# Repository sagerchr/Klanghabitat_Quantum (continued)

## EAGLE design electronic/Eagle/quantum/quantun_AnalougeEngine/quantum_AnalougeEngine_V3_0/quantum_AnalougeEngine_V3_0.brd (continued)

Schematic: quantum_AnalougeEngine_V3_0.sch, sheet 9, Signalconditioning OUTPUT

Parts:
C17, C18, C19, C20, C23, C24: 100nF; C0603
D1, D2, D6, D7: 4148; SOD323-R
IC5, IC6, IC7: NE5532D; SO08
R1, R2, R4, R6, R13, R16, R31, R32: 100k; R0805
R3, R15: 0R; R0805
R5, R30: 180k; R0805
TP03, TP04: TPTHT; THT_PIN

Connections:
ADC1-IN3: R3.2, TP03.P$1; also elsewhere on the board
ADC2-IN10: R15.2, TP04.P$1; also elsewhere on the board
AGND: C17.2, C18.2, C19.2, C20.2, C23.2, C24.2, IC5.3 (+IN), IC5.5 (+IN), IC6.3 (+IN), IC6.5 (+IN); also elsewhere on the board
L/M_OUT(VCA1_OUT): IC7.3 (+IN); also elsewhere on the board
unnamed: D2.C, IC5.2 (-IN), R1.2, R6.1
unnamed: D1.C, D2.A, IC5.1 (OUT)
unnamed: D1.A, R4.1, R6.2
unnamed: IC5.6 (-IN), R4.2, R5.2, R13.1
unnamed: IC5.7 (OUT), R3.1, R13.2
unnamed: D7.C, IC6.2 (-IN), R2.2, R31.1
unnamed: D6.C, D7.A, IC6.1 (OUT)
unnamed: D6.A, R16.1, R31.2
unnamed: IC6.6 (-IN), R16.2, R30.2, R32.1
unnamed: IC6.7 (OUT), R15.1, R32.2
NET11: IC7.1 (OUT), IC7.2 (-IN), R1.1, R5.1
NET22: IC7.6 (-IN), IC7.7 (OUT), R2.1, R30.1
R/S_OUT(VCA2_OUT): IC7.5 (+IN); also elsewhere on the board
V+: C18.1, C20.1, C23.1, IC5.8 (V+), IC6.8 (V+), IC7.8 (V+); also elsewhere on the board
V-: C17.1, C19.1, C24.1, IC5.4 (V-), IC6.4 (V-), IC7.4 (V-); also elsewhere on the board

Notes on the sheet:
Präzisionsgleichrichter

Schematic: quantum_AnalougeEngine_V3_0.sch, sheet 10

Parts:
U1: NUCLEO-F429ZI; MODULE_NUCLEO-F429ZI

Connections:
+9V: U1.CN8_15 (VIN); also elsewhere on the board
ADC1-IN0: U1.CN11_28 (PA0); also elsewhere on the board
ADC1-IN3: U1.CN12_37 (PA3); also elsewhere on the board
ADC1-IN6: U1.CN12_13 (PA6)
ADC2-IN9: U1.CN12_24 (PB1); also elsewhere on the board
ADC2-IN10: U1.CN11_38 (PC0); also elsewhere on the board
ADC2-IN12: U1.CN11_35 (PC2)
ADC3-IN13: U1.CN11_37 (PC3)
ADC3-IN14: U1.CN12_38 (PF4)
ADC3-IN15: U1.CN12_36 (PF5)
DAC_OUT1: U1.CN11_32 (PA4); also elsewhere on the board
DAC_OUT2: U1.CN12_11 (PA5); also elsewhere on the board
DGND: U1.CN8_11 (GND_CN8), U1.CN8_13 (GND_CN8); also elsewhere on the board
RELAIS1: U1.CN11_58 (PG1); also elsewhere on the board
RELAIS2: U1.CN11_62 (PE6); also elsewhere on the board
RELAIS3: U1.CN11_64 (PG15); also elsewhere on the board
RELAIS4: U1.CN11_66 (PG10); also elsewhere on the board
RELAIS5: U1.CN11_65 (PG12); also elsewhere on the board
RELAIS6: U1.CN11_63 (PG9); also elsewhere on the board
USART6_TX: U1.CN12_4 (PC6)
USRAT6_RX: U1.CN12_19 (PC7)

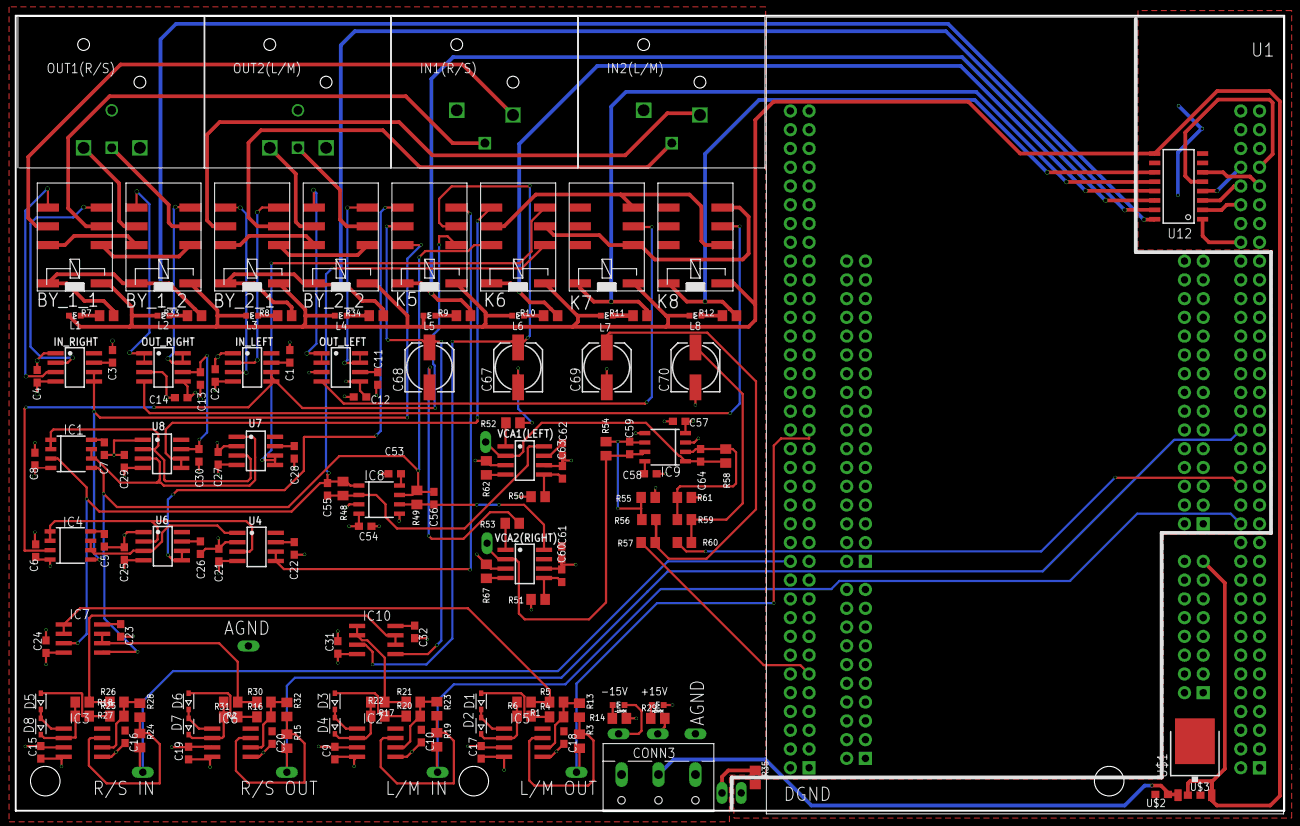
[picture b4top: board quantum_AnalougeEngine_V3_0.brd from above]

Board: 4 copper layers, 171.7 x 107.6 mm, 167 parts (0 on the bottom side), 111 nets.

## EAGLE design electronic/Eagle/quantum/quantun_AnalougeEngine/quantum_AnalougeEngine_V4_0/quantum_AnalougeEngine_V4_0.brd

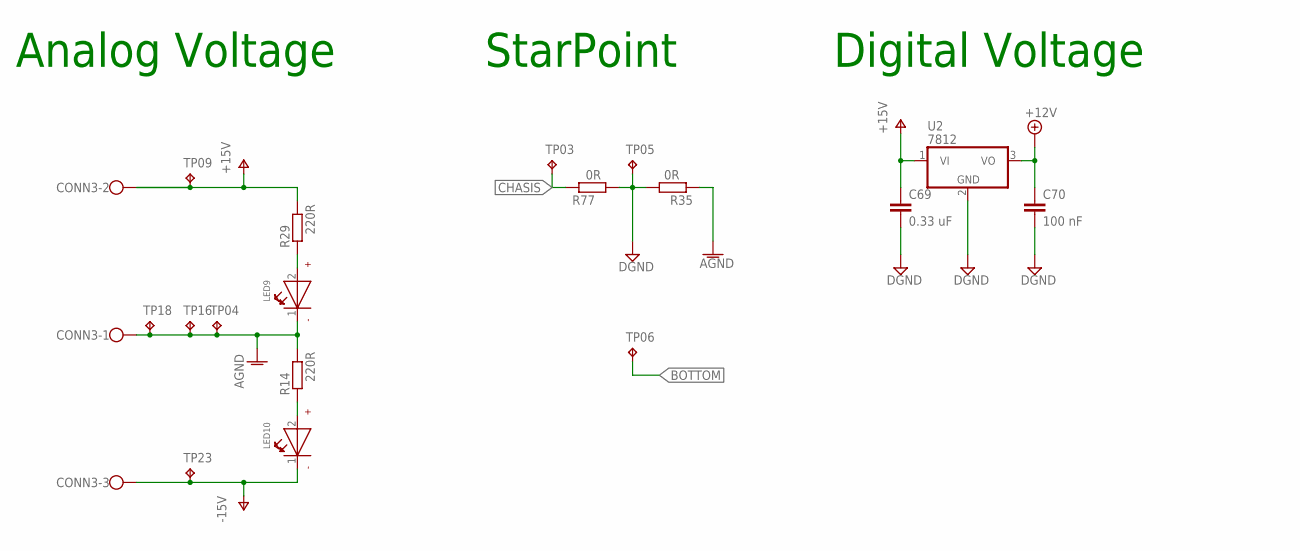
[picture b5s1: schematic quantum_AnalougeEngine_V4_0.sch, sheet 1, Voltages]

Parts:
C69: 0.33 uF; C0603
C70: 100 nF; C0603
CONN3: SCHRAUBKLEMME_3POL; W237-103
LED9, LED10: LED_GREEN_SMD; WL-SMCW_0603
R14, R29: 220R; R0603
R35, R77: 0R; R0603
TP03, TP04, TP05, TP06, TP09, TP16, TP18, TP23: TPTHT; THT_PIN
U2: 7812; TO252

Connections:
+12V: C70.1, U2.3 (VO); also elsewhere on the board
AGND: CONN3.1, LED9.1 (-), R14.2, R35.1, TP04.P$1, TP16.P$1, TP18.P$1; also elsewhere on the board
BOTTOM: TP06.P$1
CHASIS: R77.1, TP03.P$1; also elsewhere on the board
DGND: C69.2, C70.2, R35.2, R77.2, TP05.P$1, U2.2 (GND); also elsewhere on the board
unnamed: LED10.2 (+), R14.1
unnamed: LED9.2 (+), R29.1
V+: C69.1, CONN3.2, R29.2, TP09.P$1, U2.1 (VI); also elsewhere on the board
V-: CONN3.3, LED10.1 (-), TP23.P$1; also elsewhere on the board

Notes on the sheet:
StarPoint
Analog Voltage
Digital Voltage

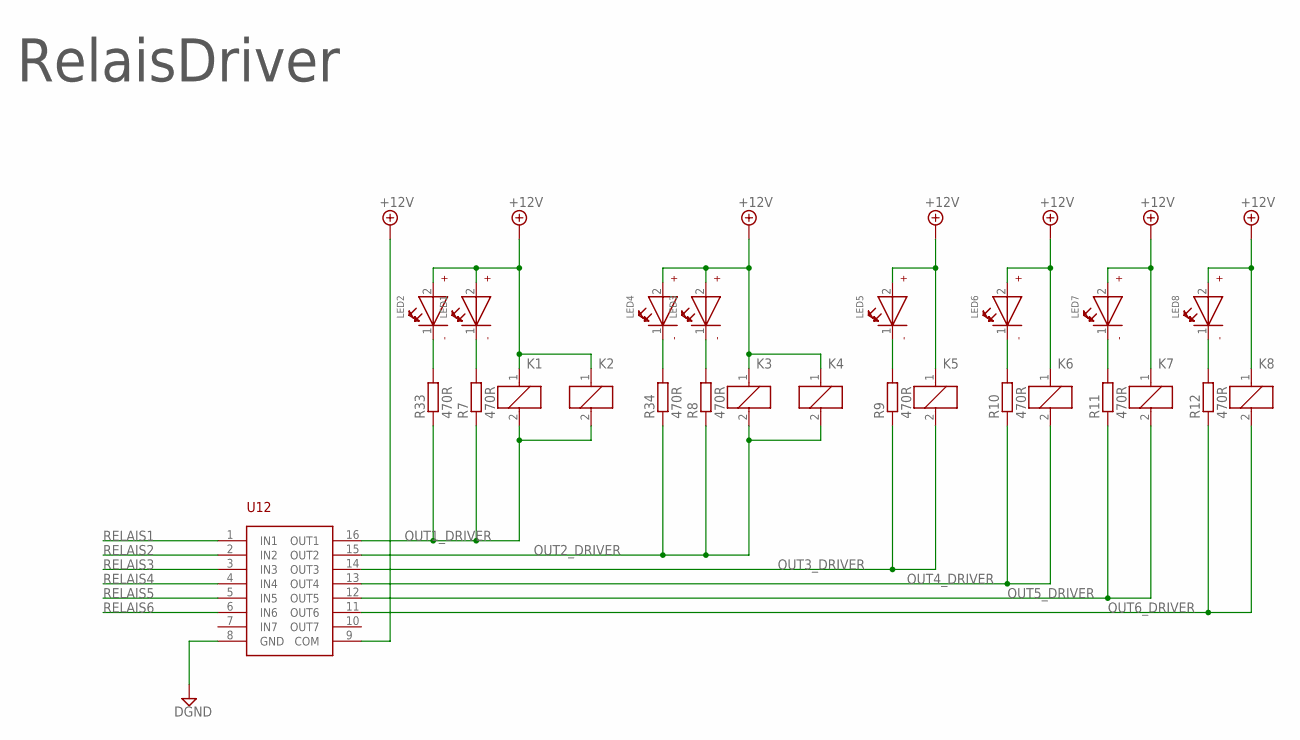
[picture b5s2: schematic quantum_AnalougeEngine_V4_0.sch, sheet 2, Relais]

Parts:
K1: K1; 351
K2: K2; 351
K3: K3; 351
K4: K4; 351
K5: K5; 351
K6: K6; 351
K7: K7; 351
K8: K8; 351
LED1, LED2, LED3, LED4, LED5, LED6, LED7, LED8: LED_BLUE_SMD; WL-SMCW_0603
R7, R8, R9, R10, R11, R12, R33, R34: 470R; R0603
U12: ULN2003; SOIC16

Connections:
+12V: K1.1, K2.1, K3.1, K4.1, K5.1, K6.1, K7.1, K8.1, LED1.2 (+), LED2.2 (+), LED3.2 (+), LED4.2 (+), LED5.2 (+), LED6.2 (+), LED7.2 (+), LED8.2 (+), U12.9 (COM); also elsewhere on the board
DGND: U12.8 (GND); also elsewhere on the board
unnamed: LED1.1 (-), R7.2
unnamed: LED3.1 (-), R8.2
unnamed: LED8.1 (-), R12.2
unnamed: LED7.1 (-), R11.2
unnamed: LED6.1 (-), R10.2
unnamed: LED5.1 (-), R9.2
unnamed: LED2.1 (-), R33.2
unnamed: LED4.1 (-), R34.2
OUT1_DRIVER: K1.2, K2.2, R7.1, R33.1, U12.16 (OUT1)
OUT2_DRIVER: K3.2, K4.2, R8.1, R34.1, U12.15 (OUT2)
OUT3_DRIVER: K5.2, R9.1, U12.14 (OUT3)
OUT4_DRIVER: K6.2, R10.1, U12.13 (OUT4)
OUT5_DRIVER: K7.2, R11.1, U12.12 (OUT5)
OUT6_DRIVER: K8.2, R12.1, U12.11 (OUT6)
RELAIS1: U12.1 (IN1); also elsewhere on the board
RELAIS2: U12.2 (IN2); also elsewhere on the board
RELAIS3: U12.3 (IN3); also elsewhere on the board
RELAIS4: U12.4 (IN4); also elsewhere on the board
RELAIS5: U12.5 (IN5); also elsewhere on the board
RELAIS6: U12.6 (IN6); also elsewhere on the board

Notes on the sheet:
RelaisDriver

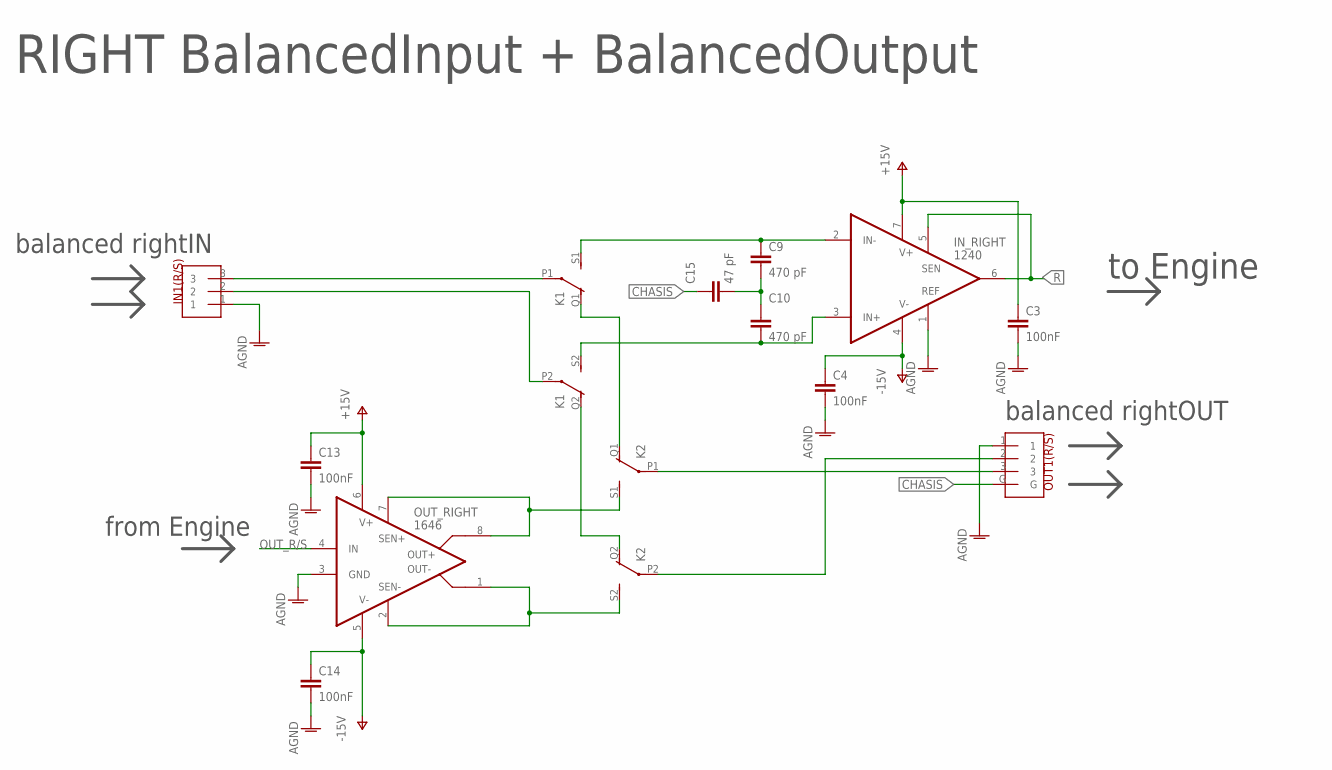
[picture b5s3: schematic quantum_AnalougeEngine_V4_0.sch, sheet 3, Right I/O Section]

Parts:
C3, C4, C13, C14: 100nF; C0603
C9, C10: 470 pF; C0603
C15: 47 pF; C0603
IN1(R/S): NEUTRIK_NC3FAH
IN_RIGHT: 1240; SO08
K1: K1; 351
K2: K2; 351
OUT1(R/S): NEUTRIK_NC3MAH
OUT_RIGHT: 1646; SO08

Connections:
AGND: C3.2, C4.2, C13.2, C14.2, IN1(R/S).1, IN_RIGHT.1 (REF), OUT1(R/S).1, OUT_RIGHT.3 (GND); also elsewhere on the board
CHASIS: C15.1, OUT1(R/S).G; also elsewhere on the board
unnamed: C9.1, IN_RIGHT.2 (IN-), K1.S1 (S)
unnamed: C10.2, IN_RIGHT.3 (IN+), K1.S2 (S)
unnamed: C9.2, C10.1, C15.2
unnamed: K1.Q1 (O), K2.Q1 (O)
unnamed: K1.Q2 (O), K2.Q2 (O)
unnamed: IN1(R/S).2, K1.P2
unnamed: IN1(R/S).3, K1.P1
unnamed: K2.P2, OUT1(R/S).2
unnamed: K2.P1, OUT1(R/S).3
OUT_R/S: OUT_RIGHT.4 (IN); also elsewhere on the board
R: IN_RIGHT.5 (SEN), IN_RIGHT.6 (OUT); also elsewhere on the board
R/S_OUT+: K2.S1 (S), OUT_RIGHT.7 (SEN+), OUT_RIGHT.8 (OUT+)
R/S_OUT-: K2.S2 (S), OUT_RIGHT.1 (OUT-), OUT_RIGHT.2 (SEN-)
V+: C3.1, C13.1, IN_RIGHT.7 (V+), OUT_RIGHT.6 (V+); also elsewhere on the board
V-: C4.1, C14.1, IN_RIGHT.4 (V-), OUT_RIGHT.5 (V-); also elsewhere on the board

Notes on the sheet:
RIGHT BalancedInput + BalancedOutput
balanced rightIN
balanced rightOUT
from Engine
to Engine

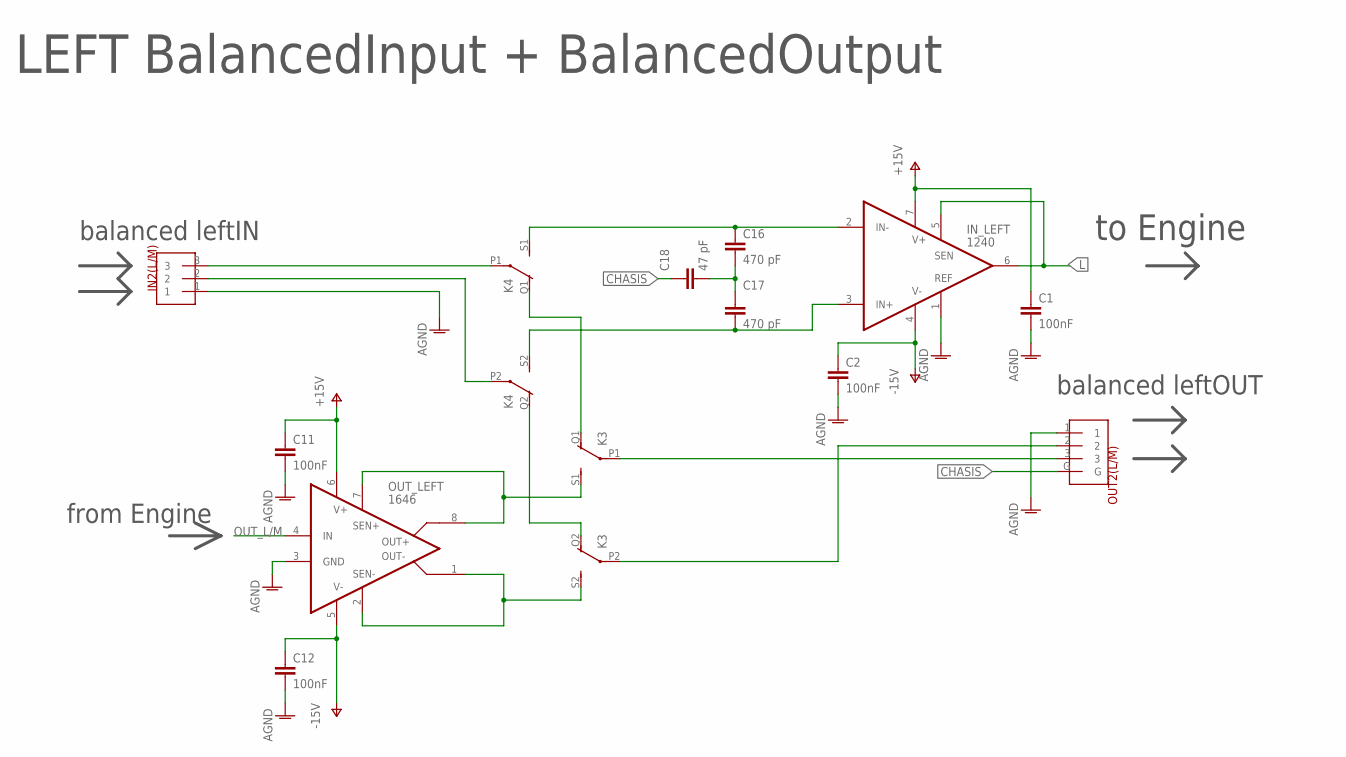
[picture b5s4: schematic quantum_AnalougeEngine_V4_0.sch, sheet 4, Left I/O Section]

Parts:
C1, C2, C11, C12: 100nF; C0603
C16, C17: 470 pF; C0603
C18: 47 pF; C0603
IN2(L/M): NEUTRIK_NC3FAH
IN_LEFT: 1240; SO08
K3: K3; 351
K4: K4; 351
OUT2(L/M): NEUTRIK_NC3MAH
OUT_LEFT: 1646; SO08

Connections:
AGND: C1.2, C2.2, C11.2, C12.2, IN2(L/M).1, IN_LEFT.1 (REF), OUT2(L/M).1, OUT_LEFT.3 (GND); also elsewhere on the board
CHASIS: C18.1, OUT2(L/M).G; also elsewhere on the board
L: IN_LEFT.5 (SEN), IN_LEFT.6 (OUT); also elsewhere on the board
L/M_OUT+: K3.S1 (S), OUT_LEFT.7 (SEN+), OUT_LEFT.8 (OUT+)
L/M_OUT-: K3.S2 (S), OUT_LEFT.1 (OUT-), OUT_LEFT.2 (SEN-)
unnamed: C17.2, IN_LEFT.3 (IN+), K4.S2 (S)
unnamed: C16.2, C17.1, C18.2
unnamed: C16.1, IN_LEFT.2 (IN-), K4.S1 (S)
unnamed: K3.P1, OUT2(L/M).3
unnamed: K3.P2, OUT2(L/M).2
unnamed: IN2(L/M).3, K4.P1
unnamed: IN2(L/M).2, K4.P2
unnamed: K3.Q1 (O), K4.Q1 (O)
unnamed: K3.Q2 (O), K4.Q2 (O)
OUT_L/M: OUT_LEFT.4 (IN); also elsewhere on the board
V+: C1.1, C11.1, IN_LEFT.7 (V+), OUT_LEFT.6 (V+); also elsewhere on the board
V-: C2.1, C12.1, IN_LEFT.4 (V-), OUT_LEFT.5 (V-); also elsewhere on the board

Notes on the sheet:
balanced leftIN
balanced leftOUT
from Engine
to Engine
LEFT BalancedInput + BalancedOutput

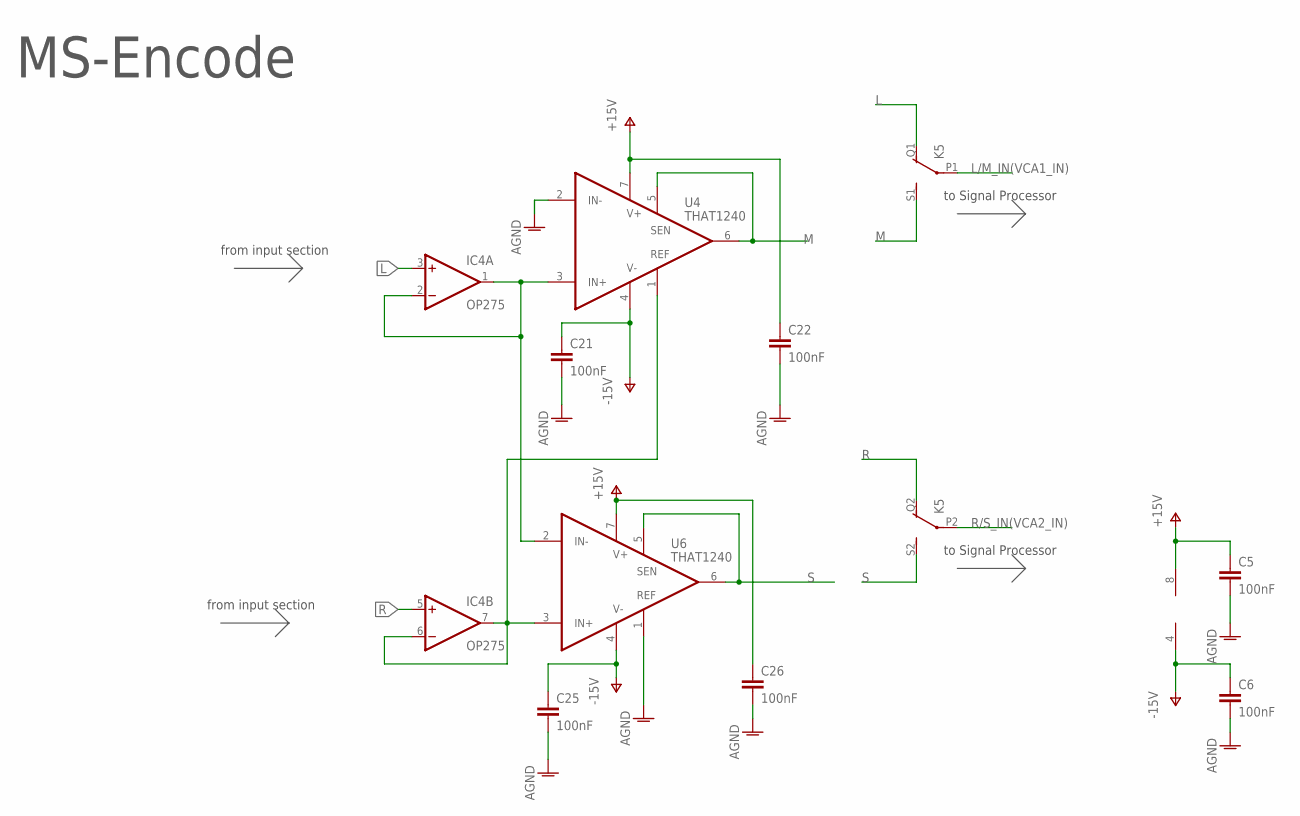
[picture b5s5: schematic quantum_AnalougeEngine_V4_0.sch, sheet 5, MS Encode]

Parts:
C5, C6, C21, C22, C25, C26: 100nF; C0603
IC4: OP275; SOIC8
K5: K5; 351
U4, U6: THAT1240; SO08

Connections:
AGND: C5.2, C6.2, C21.2, C22.2, C25.2, C26.2, U4.2 (IN-), U6.1 (REF); also elsewhere on the board
L: IC4.3 (+IN), K5.Q1 (O); also elsewhere on the board
L/M_IN(VCA1_IN): K5.P1; also elsewhere on the board
M: K5.S1 (S), U4.5 (SEN), U4.6 (OUT)
unnamed: IC4.1 (OUT), IC4.2 (-IN), U4.3 (IN+), U6.2 (IN-)
unnamed: IC4.6 (-IN), IC4.7 (OUT), U4.1 (REF), U6.3 (IN+)
R: IC4.5 (+IN), K5.Q2 (O); also elsewhere on the board
R/S_IN(VCA2_IN): K5.P2; also elsewhere on the board
S: K5.S2 (S), U6.5 (SEN), U6.6 (OUT)
V+: C5.1, C22.1, C26.1, IC4.8 (V+), U4.7 (V+), U6.7 (V+); also elsewhere on the board
V-: C6.1, C21.1, C25.1, IC4.4 (V-), U4.4 (V-), U6.4 (V-); also elsewhere on the board

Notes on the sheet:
to Signal Processor
MS-Encode
from input section

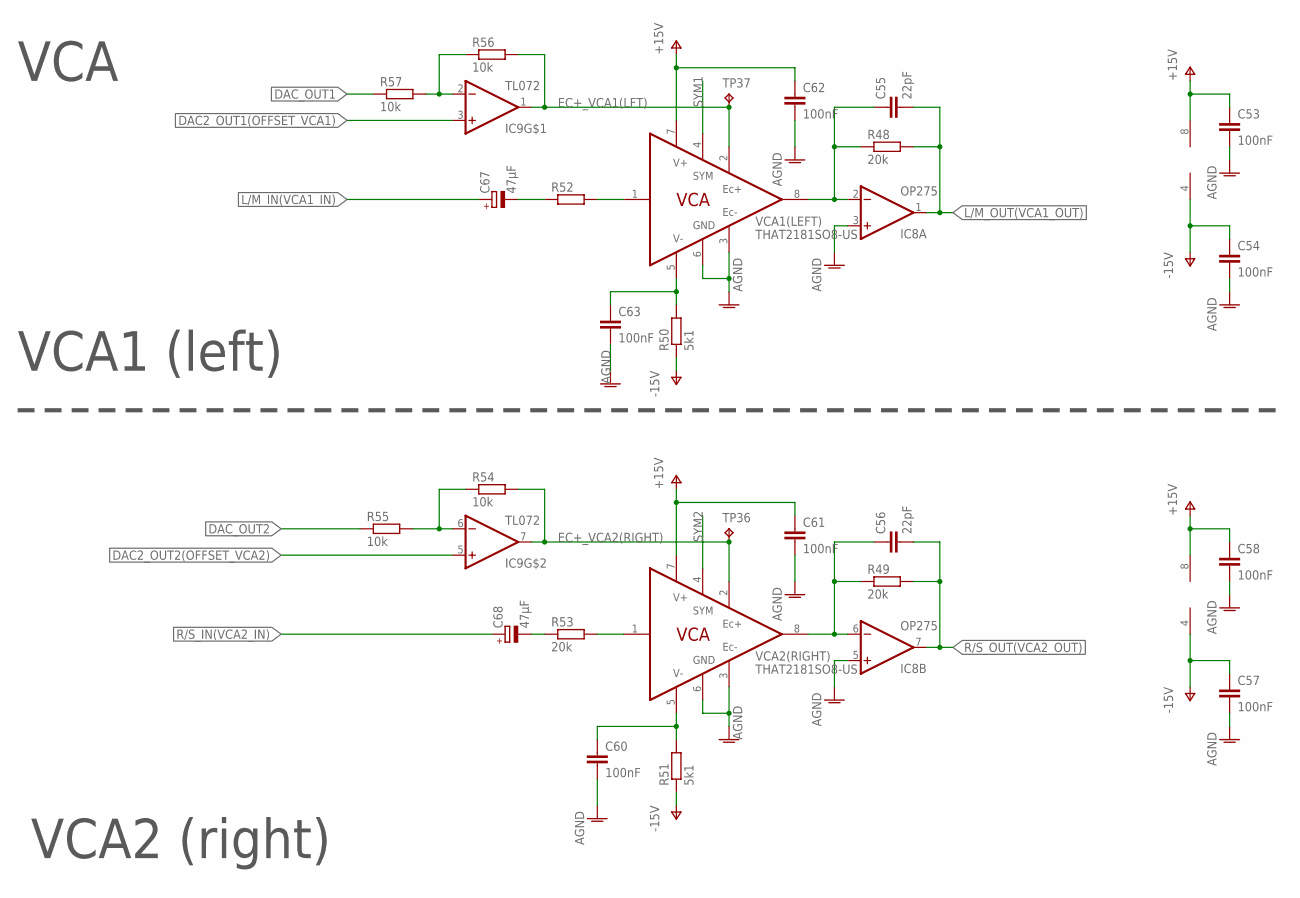
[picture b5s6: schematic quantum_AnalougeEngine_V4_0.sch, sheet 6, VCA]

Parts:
C53, C54, C57, C58, C60, C61, C62, C63: 100nF; C0603
C55, C56: 22pF; C0603
C67, C68: 47µF; CAPAE400X550N
IC8: OP275; SOIC8
IC9: TL072; SOIC8
R48, R49, R52, R53: 20k; R0603
R50, R51: 5k1; R0603
R54, R55, R56, R57: 10k; R0603
TP36, TP37: TPTHT; THT_PIN
VCA1(LEFT), VCA2(RIGHT): THAT2181SO8-US; SO08

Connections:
AGND: C53.2, C54.2, C57.2, C58.2, C60.2, C61.2, C62.2, C63.2, IC8.3 (+IN), IC8.5 (+IN), VCA1(LEFT).3 (EC-), VCA1(LEFT).6 (GND), VCA2(RIGHT).3 (EC-), VCA2(RIGHT).6 (GND); also elsewhere on the board
DAC2_OUT1(OFFSET_VCA1): IC9.3 (+IN); also elsewhere on the board
DAC2_OUT2(OFFSET_VCA2): IC9.5 (+IN); also elsewhere on the board
DAC_OUT1: R57.1; also elsewhere on the board
DAC_OUT2: R55.1; also elsewhere on the board
EC+_VCA1(LFT): IC9.1 (OUT), R56.2, TP37.P$1, VCA1(LEFT).2 (EC+)
EC+_VCA2(RIGHT): IC9.7 (OUT), R54.2, TP36.P$1, VCA2(RIGHT).2 (EC+)
L/M_IN(VCA1_IN): C67.1 (+); also elsewhere on the board
L/M_OUT(VCA1_OUT): C55.2, IC8.1 (OUT), R48.2; also elsewhere on the board
unnamed: IC9.2 (-IN), R56.1, R57.2
unnamed: C55.1, IC8.2 (-IN), R48.1, VCA1(LEFT).8 (OUT)
unnamed: R52.2, VCA1(LEFT).1 (IN)
unnamed: C67.2 (-), R52.1
unnamed: C56.1, IC8.6 (-IN), R49.1, VCA2(RIGHT).8 (OUT)
unnamed: C60.1, R51.2, VCA2(RIGHT).5 (V-)
unnamed: C68.2 (-), R53.1
unnamed: R53.2, VCA2(RIGHT).1 (IN)
unnamed: C63.1, R50.2, VCA1(LEFT).5 (V-)
unnamed: IC9.6 (-IN), R54.1, R55.2
R/S_IN(VCA2_IN): C68.1 (+); also elsewhere on the board
R/S_OUT(VCA2_OUT): C56.2, IC8.7 (OUT), R49.2; also elsewhere on the board
SYM1: VCA1(LEFT).4 (SYM); also elsewhere on the board
SYM2: VCA2(RIGHT).4 (SYM); also elsewhere on the board
V+: C53.1, C58.1, C61.1, C62.1, IC8.8 (V+), IC9.8 (V+), VCA1(LEFT).7 (V+), VCA2(RIGHT).7 (V+); also elsewhere on the board
V-: C54.1, C57.1, IC8.4 (V-), IC9.4 (V-), R50.1, R51.1; also elsewhere on the board

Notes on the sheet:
VCA
VCA1 (left)
VCA2 (right)

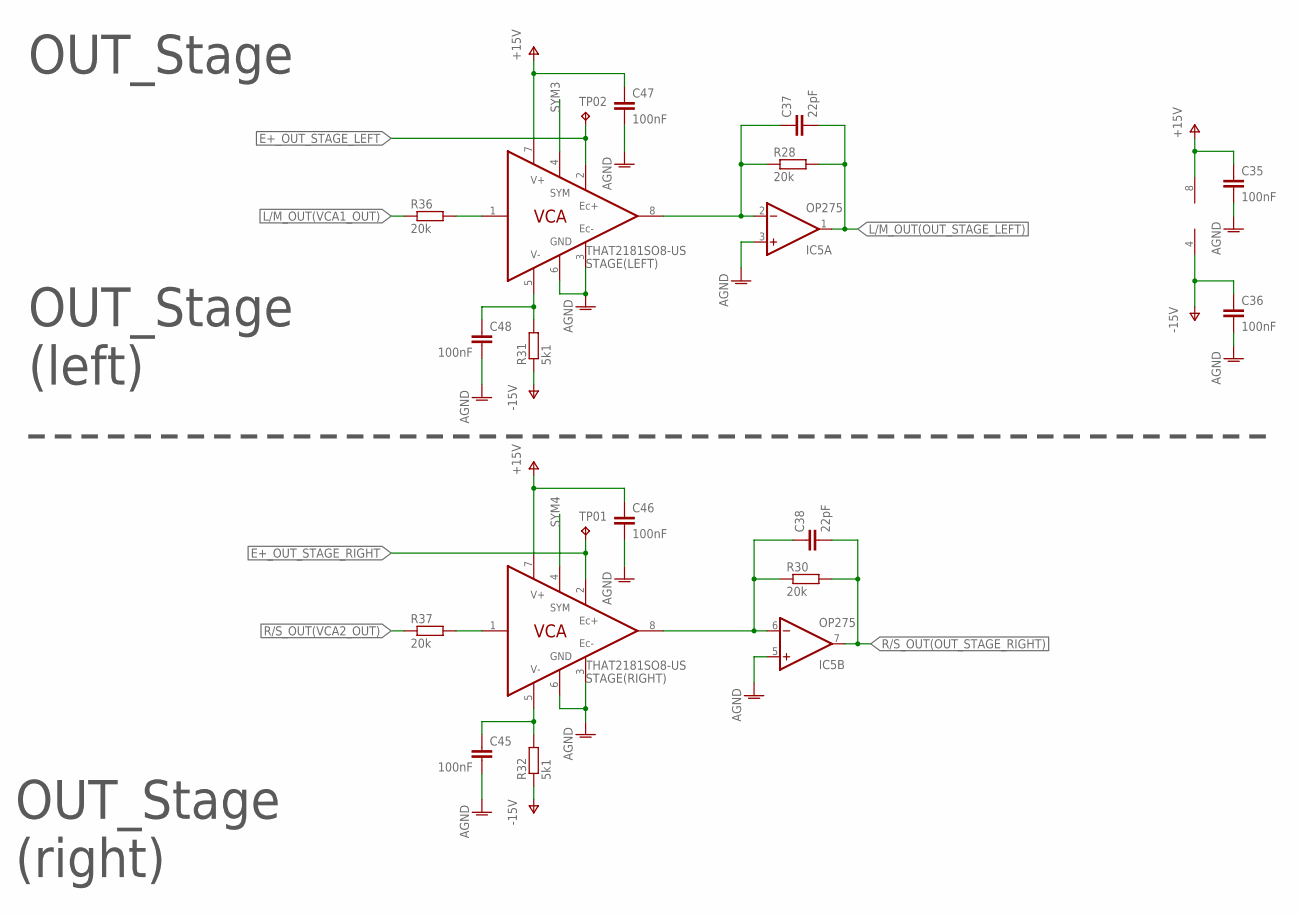
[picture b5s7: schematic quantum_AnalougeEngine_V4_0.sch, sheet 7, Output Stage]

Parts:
C35, C36, C45, C46, C47, C48: 100nF; C0603
C37, C38: 22pF; C0603
IC5: OP275; SOIC8
R28, R30, R36, R37: 20k; R0603
R31, R32: 5k1; R0603
STAGE(LEFT): THAT2181SO8-US; SO08
STAGE(RIGHT): THAT2181SO8-US; SO08
TP01, TP02: TPTHT; THT_PIN

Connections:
AGND: C35.2, C36.2, C45.2, C46.2, C47.2, C48.2, IC5.3 (+IN), IC5.5 (+IN), STAGE(LEFT).3 (EC-), STAGE(LEFT).6 (GND), STAGE(RIGHT).3 (EC-), STAGE(RIGHT).6 (GND); also elsewhere on the board
E+_OUT_STAGE_LEFT: STAGE(LEFT).2 (EC+), TP02.P$1; also elsewhere on the board
E+_OUT_STAGE_RIGHT: STAGE(RIGHT).2 (EC+), TP01.P$1; also elsewhere on the board
L/M_OUT(OUT_STAGE_LEFT): C37.2, IC5.1 (OUT), R28.2; also elsewhere on the board
L/M_OUT(VCA1_OUT): R36.1; also elsewhere on the board
unnamed: C37.1, IC5.2 (-IN), R28.1, STAGE(LEFT).8 (OUT)
unnamed: C38.1, IC5.6 (-IN), R30.1, STAGE(RIGHT).8 (OUT)
unnamed: C45.1, R32.2, STAGE(RIGHT).5 (V-)
unnamed: R36.2, STAGE(LEFT).1 (IN)
unnamed: R37.2, STAGE(RIGHT).1 (IN)
unnamed: C48.1, R31.2, STAGE(LEFT).5 (V-)
R/S_OUT(OUT_STAGE_RIGHT): C38.2, IC5.7 (OUT), R30.2; also elsewhere on the board
R/S_OUT(VCA2_OUT): R37.1; also elsewhere on the board
SYM3: STAGE(LEFT).4 (SYM); also elsewhere on the board
SYM4: STAGE(RIGHT).4 (SYM); also elsewhere on the board
V+: C35.1, C46.1, C47.1, IC5.8 (V+), STAGE(LEFT).7 (V+), STAGE(RIGHT).7 (V+); also elsewhere on the board
V-: C36.1, IC5.4 (V-), R31.1, R32.1; also elsewhere on the board

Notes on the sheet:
OUT_Stage
OUT_Stage (left)
OUT_Stage (right)

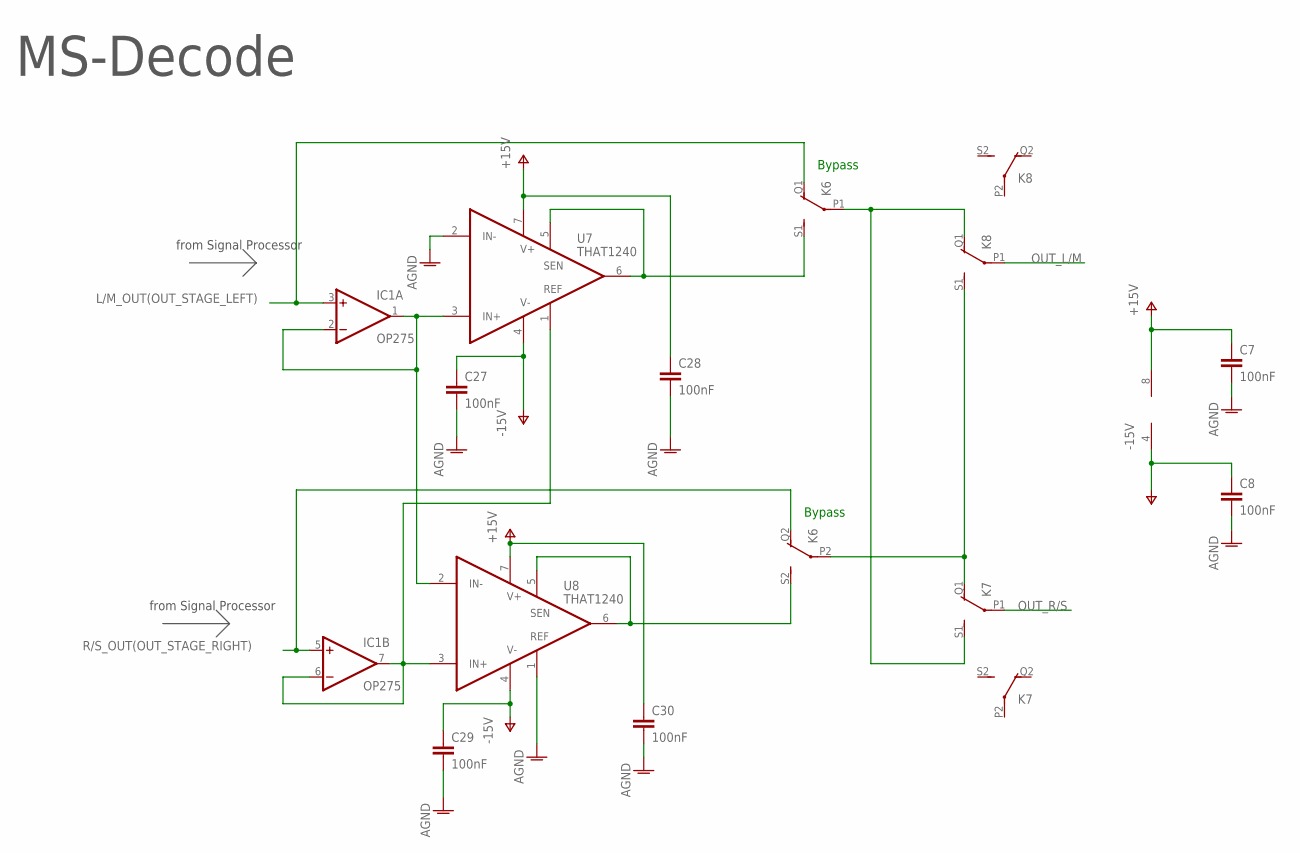
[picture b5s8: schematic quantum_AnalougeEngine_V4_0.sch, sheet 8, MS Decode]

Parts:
C7, C8, C27, C28, C29, C30: 100nF; C0603
IC1: OP275; SOIC8
K6: K6; 351
K7: K7; 351
K8: K8; 351
U7, U8: THAT1240; SO08

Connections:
AGND: C7.2, C8.2, C27.2, C28.2, C29.2, C30.2, U7.2 (IN-), U8.1 (REF); also elsewhere on the board
L/M_OUT(OUT_STAGE_LEFT): IC1.3 (+IN), K6.Q1 (O); also elsewhere on the board
M1: K6.S1 (S), U7.5 (SEN), U7.6 (OUT)
unnamed: K6.P1, K7.S1 (S), K8.Q1 (O)
unnamed: K6.P2, K7.Q1 (O), K8.S1 (S)
unnamed: IC1.6 (-IN), IC1.7 (OUT), U7.1 (REF), U8.3 (IN+)
unnamed: IC1.1 (OUT), IC1.2 (-IN), U7.3 (IN+), U8.2 (IN-)
OUT_L/M: K8.P1; also elsewhere on the board
OUT_R/S: K7.P1; also elsewhere on the board
R/S_OUT(OUT_STAGE_RIGHT): IC1.5 (+IN), K6.Q2 (O); also elsewhere on the board
S1: K6.S2 (S), U8.5 (SEN), U8.6 (OUT)
V+: C7.1, C28.1, C30.1, IC1.8 (V+), U7.7 (V+), U8.7 (V+); also elsewhere on the board
V-: C8.1, C27.1, C29.1, IC1.4 (V-), U7.4 (V-), U8.4 (V-); also elsewhere on the board

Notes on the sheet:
from Signal Processor
MS-Decode
Bypass

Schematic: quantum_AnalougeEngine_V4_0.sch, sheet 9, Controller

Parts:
U1: NUCLEO-F429ZI; MODULE_NUCLEO-F429ZI

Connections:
+3V3_STM32: U1.CN11_16 (+3.3V); also elsewhere on the board
+5V_STM32: U1.CN11_18 (+5V); also elsewhere on the board
+12V: U1.CN8_15 (VIN); also elsewhere on the board
ADC1-IN0: U1.CN11_28 (PA0); also elsewhere on the board
ADC1-IN3: U1.CN12_37 (PA3); also elsewhere on the board
ADC1-IN6: U1.CN12_13 (PA6)
ADC2-IN9: U1.CN12_24 (PB1)
ADC2-IN10: U1.CN11_38 (PC0)
ADC2-IN12: U1.CN11_35 (PC2)
ADC3-IN13: U1.CN11_37 (PC3)
ADC3-IN14: U1.CN12_38 (PF4)
ADC3-IN15: U1.CN12_36 (PF5)
BUSY: U1.CN11_44 (PG3); also elsewhere on the board
CS: U1.CN11_45 (PD7); also elsewhere on the board
CS_DAC1: U1.CN12_27 (PB4); also elsewhere on the board
CS_DAC2: U1.CN12_29 (PB5); also elsewhere on the board
CV_A_B: U1.CN11_3 (PC12); also elsewhere on the board
DAC_OUT1: U1.CN11_32 (PA4); also elsewhere on the board
DAC_OUT2: U1.CN12_11 (PA5); also elsewhere on the board
DB0: U1.CN10_33 (D34/PE0/TIMER_B_ETR), U1.CN12_64 (PE0); also elsewhere on the board
DB1: U1.CN11_61 (PE1); also elsewhere on the board
DB2: U1.CN9_14 (D56/PE2/SAI_A_MCLK), U1.CN10_25 (D31/PE2); also elsewhere on the board
DB3: U1.CN9_22 (D60/PE3/SAI_B_SD), U1.CN11_47 (PE3); also elsewhere on the board
DB4: U1.CN9_16 (D57/PE4/SAI_A_FS); also elsewhere on the board
DB5: U1.CN9_18 (D58/PE5/SAI_A_SCK); also elsewhere on the board
DB6: U1.CN9_20 (D59/PE6/SAI_A_SD), U1.CN11_62 (PE6); also elsewhere on the board
DB7: U1.CN10_20 (D41/PE7/TIMER_A_ETR), U1.CN12_44 (PE7); also elsewhere on the board
DB8: U1.CN10_18 (D42/PE8/TIMER_A_PWM1N); also elsewhere on the board
DB9: U1.CN10_4 (D6/PE9/TIMER_A_PWM1), U1.CN12_52 (PE9); also elsewhere on the board
DB10: U1.CN10_24 (D40/PE10/TIMER_A_PWM2N), U1.CN12_47 (PE10); also elsewhere on the board
DB11: U1.CN10_6 (D5/PE11/TIMER_A_PWM2); also elsewhere on the board
DB12: U1.CN10_26 (D39/PE12/TIMER_A_PWM3N), U1.CN12_49 (PE12); also elsewhere on the board
DB13: U1.CN10_10 (D3/PE13/TIMER_A_PWM3), U1.CN12_55 (PE13); also elsewhere on the board
DB14: U1.CN10_28 (D38/PE14), U1.CN12_51 (PE14); also elsewhere on the board
DB15: U1.CN12_53 (PE15); also elsewhere on the board
DGND: U1.CN8_11 (GND_CN8), U1.CN8_13 (GND_CN8); also elsewhere on the board
DIN_DAC: U1.CN9_5 (A2/PC3); also elsewhere on the board
FRST: U1.CN11_43 (PD6); also elsewhere on the board
OS0: U1.CN12_2 (PC8); also elsewhere on the board
OS1: U1.CN12_1 (PC9); also elsewhere on the board
OS2: U1.CN11_1 (PC10); also elsewhere on the board
RANGE: U1.CN11_2 (PC11); also elsewhere on the board
RD: U1.CN11_4 (PD2); also elsewhere on the board
RELAIS1: U1.CN11_58 (PG1); also elsewhere on the board
RELAIS2: U1.CN11_59 (PG0); also elsewhere on the board
RELAIS3: U1.CN11_64 (PG15); also elsewhere on the board
RELAIS4: U1.CN11_66 (PG10); also elsewhere on the board
RELAIS5: U1.CN11_65 (PG12); also elsewhere on the board
RELAIS6: U1.CN11_63 (PG9); also elsewhere on the board
RESET: U1.CN11_42 (PG2); also elsewhere on the board
SCLK_DAC: U1.CN12_25 (PB10); also elsewhere on the board
SWCLK: U1.CN11_15 (PA14)
SWDIO: U1.CN11_13 (PA13)
USART6_TX: U1.CN12_4 (PC6)
USRAT6_RX: U1.CN12_19 (PC7)

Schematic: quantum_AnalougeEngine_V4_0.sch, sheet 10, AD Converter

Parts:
R1, R4, R5, R6, R13, R15, R16, R17, R18, R19, R20, R21, R22, R23, R24, R25, R26, R27: 10k; R0603
R2, R3: 100k; R0603
U3: AD7606_EVALBOARD

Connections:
+3V3_STM32: R1.2; also elsewhere on the board
+5V_STM32: U3.+5V; also elsewhere on the board
ADC1-IN0: R3.1, R4.2; also elsewhere on the board
ADC1-IN3: R1.1, R2.2; also elsewhere on the board
AGND: R4.1, R6.1, R15.1, R16.1, R23.1, R24.1, R25.1, R26.1, R27.1, U3.G1, U3.G2, U3.G3, U3.G4, U3.G5, U3.G6, U3.G7, U3.G8; also elsewhere on the board
BUSY: U3.BUSY; also elsewhere on the board
CS: U3.CS; also elsewhere on the board
CV_A_B: U3.CVA, U3.CVB; also elsewhere on the board
DB0: U3.DB0; also elsewhere on the board
DB1: U3.DB1; also elsewhere on the board
DB2: U3.DB2; also elsewhere on the board
DB3: U3.DB3; also elsewhere on the board
DB4: U3.DB4; also elsewhere on the board
DB5: U3.DB5; also elsewhere on the board
DB6: U3.DB6; also elsewhere on the board
DB7: U3.DB7; also elsewhere on the board
DB8: U3.DB8; also elsewhere on the board
DB9: U3.DB9; also elsewhere on the board
DB10: U3.DB10; also elsewhere on the board
DB11: U3.DB11; also elsewhere on the board
DB12: U3.DB12; also elsewhere on the board
DB13: U3.DB13; also elsewhere on the board
DB14: U3.DB14; also elsewhere on the board
DB15: U3.DB15; also elsewhere on the board
DGND: U3.GND; also elsewhere on the board
FRST: U3.FRST; also elsewhere on the board
L/M_IN(VCA1_IN): R5.1; also elsewhere on the board
L/M_OUT(OUT_STAGE_LEFT): R19.1; also elsewhere on the board
L/M_OUT(VCA1_OUT): R17.1; also elsewhere on the board
unnamed: R5.2, R6.2, U3.V1
unnamed: R13.2, R15.2, U3.V2
unnamed: R16.2, R17.2, U3.V3
unnamed: R18.2, R23.2, U3.V4
unnamed: R19.2, R24.2, U3.V5
unnamed: R20.2, R25.2, U3.V6
unnamed: R21.2, R26.2, U3.V7
unnamed: R22.2, R27.2, U3.V8
OS0: U3.OS0; also elsewhere on the board
OS1: U3.OS1; also elsewhere on the board
OS2: U3.OS2; also elsewhere on the board
R/S_IN(VCA2_IN): R13.1; also elsewhere on the board
R/S_OUT(OUT_STAGE_RIGHT): R20.1; also elsewhere on the board
R/S_OUT(VCA2_OUT): R18.1; also elsewhere on the board
RANGE: U3.RANGE; also elsewhere on the board
RD: U3.RD; also elsewhere on the board
RESET: U3.RST; also elsewhere on the board
V+: R3.2; also elsewhere on the board
V-: R2.1; also elsewhere on the board
VIO: U3.VIO

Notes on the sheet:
AD Converter
measure positive supply voltage
measure negative supply voltage

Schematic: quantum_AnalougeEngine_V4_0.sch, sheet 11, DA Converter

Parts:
C19, C20, C23, C24, C43, C49, C50: 100nF; C0603
C31, C32, C33, C34, C39, C40, C44: 10 µF; CAPAE400X550N
IC2, IC3: DAC084S085CIMM_NOPB; SOP50P490X110-10N
IC7: TL072; SOIC8
R38, R41, R44, R64: 51k; R0603
R39, R42, R45, R65: 51R; R0603
R40, R43, R63, R66: 90k9; R0603
R46, R58, R60, R61, R62, R67, R68, R69, R70, R71, R72, R73, R74, R75: 10k; R0603
R47, R76: 1k8; R0603
R59: 56k; R0603
Z1: BZT52C2V0T-7; SODFL1608X65N

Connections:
0,5V_DAC: IC7.3 (+IN), IC7.5 (+IN), R60.2, R61.1
1V_DAC: C20.1, C23.1, C24.1, C32.1 (+), C33.1 (+), C34.1 (+), IC2.7 (VREFIN), IC3.7 (VREFIN), R61.2, R68.1, R69.2
2V_DAC_REF: R67.1, R68.2, Z1.1 (K)
+5V_STM32: C19.1, C31.1 (+), C43.1, C44.1 (+), IC2.1 (VA), IC3.1 (VA); also elsewhere on the board
.: IC7.7 (OUT), R59.2, R72.2
...: IC7.1 (OUT), R71.2, R73.2
AGND: C20.2, C23.2, C24.2, C32.2 (-), C33.2 (-), C34.2 (-), C39.2 (-), C40.2 (-), C49.2, C50.2, R39.1, R42.1, R45.1, R46.1, R47.1, R58.1, R60.1, R65.1, R69.1, R76.1, Z1.2 (A); also elsewhere on the board
CS_DAC1: IC2.9 (!SYNC); also elsewhere on the board
CS_DAC2: IC3.9 (!SYNC); also elsewhere on the board
DAC2_OUT1(OFFSET_VCA1): C39.1 (+), R74.2, R76.2; also elsewhere on the board
DAC2_OUT2(OFFSET_VCA2): C40.1 (+), R47.2, R75.2; also elsewhere on the board
DAC2_OUT3: IC3.4 (VOUTC), R62.1
DAC2_OUT4: IC3.5 (VOUTD), R70.1
DGND: C19.2, C31.2 (-), C43.2, C44.2 (-), IC2.6 (GND), IC3.6 (GND); also elsewhere on the board
DIN_DAC: IC2.8 (DIN), IC3.8 (DIN); also elsewhere on the board
E+_OUT_STAGE_LEFT: R46.2, R73.1; also elsewhere on the board
E+_OUT_STAGE_RIGHT: R58.2, R59.1; also elsewhere on the board
unnamed: IC2.2 (VOUTA), R38.2
unnamed: IC2.3 (VOUTB), R41.2
unnamed: IC2.4 (VOUTC), R44.2
unnamed: IC2.5 (VOUTD), R64.2
unnamed: IC3.2 (VOUTA), R74.1
unnamed: IC3.3 (VOUTB), R75.1
unnamed: IC7.2 (-IN), R62.2, R71.1
unnamed: IC7.6 (-IN), R70.2, R72.1
SCLK_DAC: IC2.10 (SCLK), IC3.10 (SCLK); also elsewhere on the board
SYM1: R38.1, R39.2, R40.2; also elsewhere on the board
SYM2: R41.1, R42.2, R43.2; also elsewhere on the board
SYM3: R44.1, R45.2, R63.2; also elsewhere on the board
SYM4: R64.1, R65.2, R66.2; also elsewhere on the board
V+: C49.1, IC7.8 (V+), R67.2; also elsewhere on the board
V-: C50.1, IC7.4 (V-), R40.1, R43.1, R63.1, R66.1; also elsewhere on the board

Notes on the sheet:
DA Converter
Attention SPI is not configured jet in CubeMX
use: SPI2: Transmit Only Master PB10: SPI2_SCK PC3: SPI2_MOSI PB4: CS_DAC1 PB5: CS_DAC2
creates CV: 0 75,75 mV +12,625 dB 128 0 mV 0 dB 255 -77,75 mV -12,625 dB
could offset the main VCA by 153 mV which means about + 25,5 dB! step size is approx. 0.1dB per bit
